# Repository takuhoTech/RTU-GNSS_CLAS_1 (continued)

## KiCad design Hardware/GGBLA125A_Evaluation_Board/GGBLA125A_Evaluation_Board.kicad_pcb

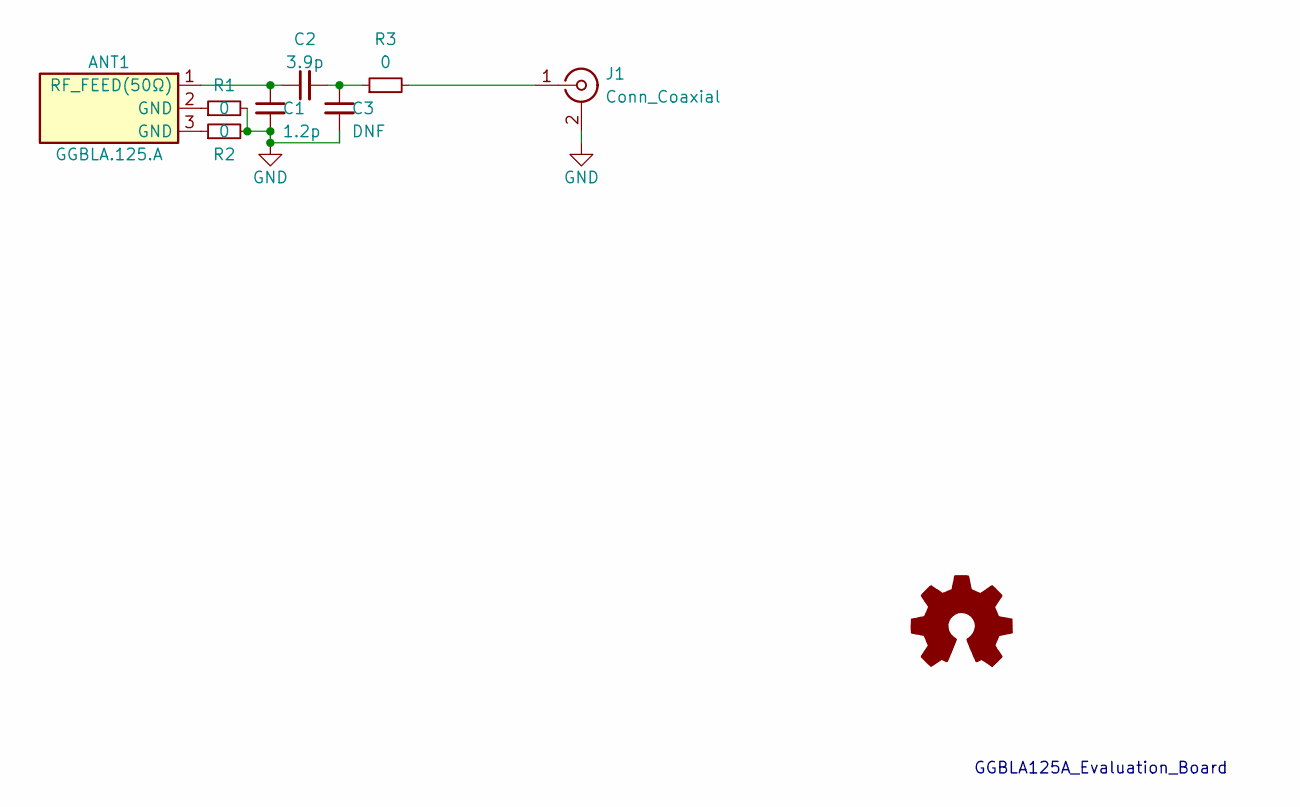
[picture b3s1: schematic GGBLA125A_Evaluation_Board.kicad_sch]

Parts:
ANT1: GGBLA.125.A; Manufacturer_Part_Number GGBLA.125.A; Mouser Part Number 960-GGBLA.125.A
C1: 1.2p; C_0402_1005Metric
C2: 3.9p; C_0402_1005Metric
C3: DNF; C_0402_1005Metric
J1: Conn_Coaxial; SMA_Samtec_SMA-J-P-X-ST-EM1_EdgeMount
R1, R2, R3: 0; R_0402_1005Metric

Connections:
GND: C1.2, C3.2, J1.2 (Ext), R1.2, R2.2
unnamed: ANT1.1 (RF_FEED(50Ω)), C1.1, C2.1
unnamed: ANT1.2 (GND), R1.1
unnamed: ANT1.3 (GND), R2.1
unnamed: C2.2, C3.1, R3.1
unnamed: J1.1 (In), R3.2

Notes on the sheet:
GGBLA125A_Evaluation_Board

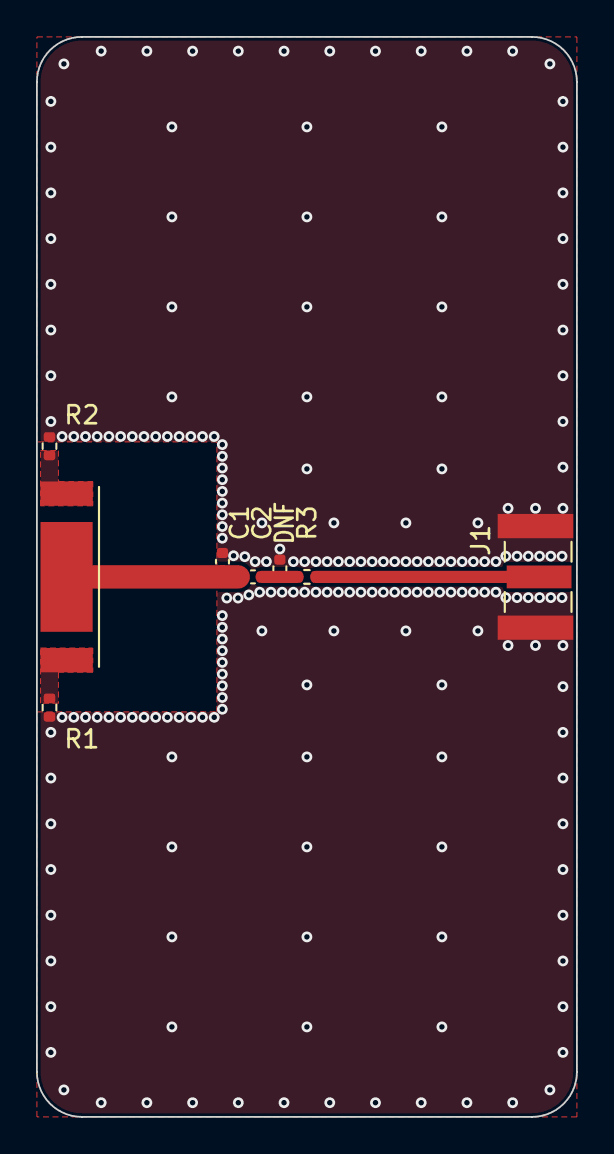
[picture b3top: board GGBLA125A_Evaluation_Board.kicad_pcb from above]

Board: 4 copper layers, 30.0 x 60.0 mm, 8 parts (0 on the bottom side), 6 nets.

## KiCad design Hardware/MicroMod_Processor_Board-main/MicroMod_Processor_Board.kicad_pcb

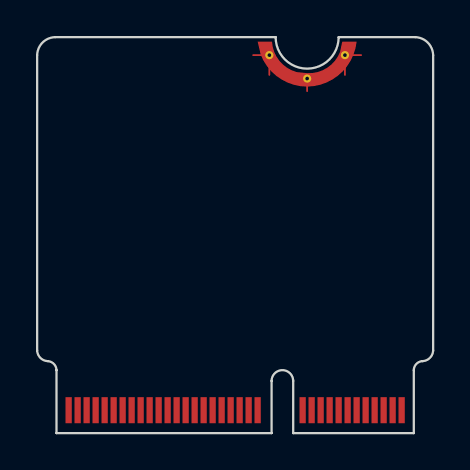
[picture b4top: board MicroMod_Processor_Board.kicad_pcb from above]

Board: 4 copper layers, 22.0 x 22.0 mm, 4 parts (0 on the bottom side), 6 nets, no tracks yet.

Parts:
FRAME1: FRAME-LEDGER; CREATIVE_COMMONS
J1: MICROMOD-2222; M.2-CARD-E-22
LOGO1: SPECIAL_INSTRUCTIONS-ORDERING; ORDERING_INSTRUCTIONS
LOGO3: OSHW-LOGOS; OSHW-LOGO-S

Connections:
3.3V: J1.2, J1.74
/16-G4/RX1/AUD_IN: J1.19, J1.48, J1.54
/17-G3/TX1/AUD_OUT: J1.17, J1.46, J1.56
/25-G1/AUD_LRCLK/SCL1: J1.42, J1.52, J1.53
/26-G2/AUD_BCLK/SDA1: J1.44, J1.50, J1.51
GND: J1.1, J1.7, J1.33, J1.36, J1.39, J1.45, J1.75, J1.GND1, J1.GND2, J1.GND3

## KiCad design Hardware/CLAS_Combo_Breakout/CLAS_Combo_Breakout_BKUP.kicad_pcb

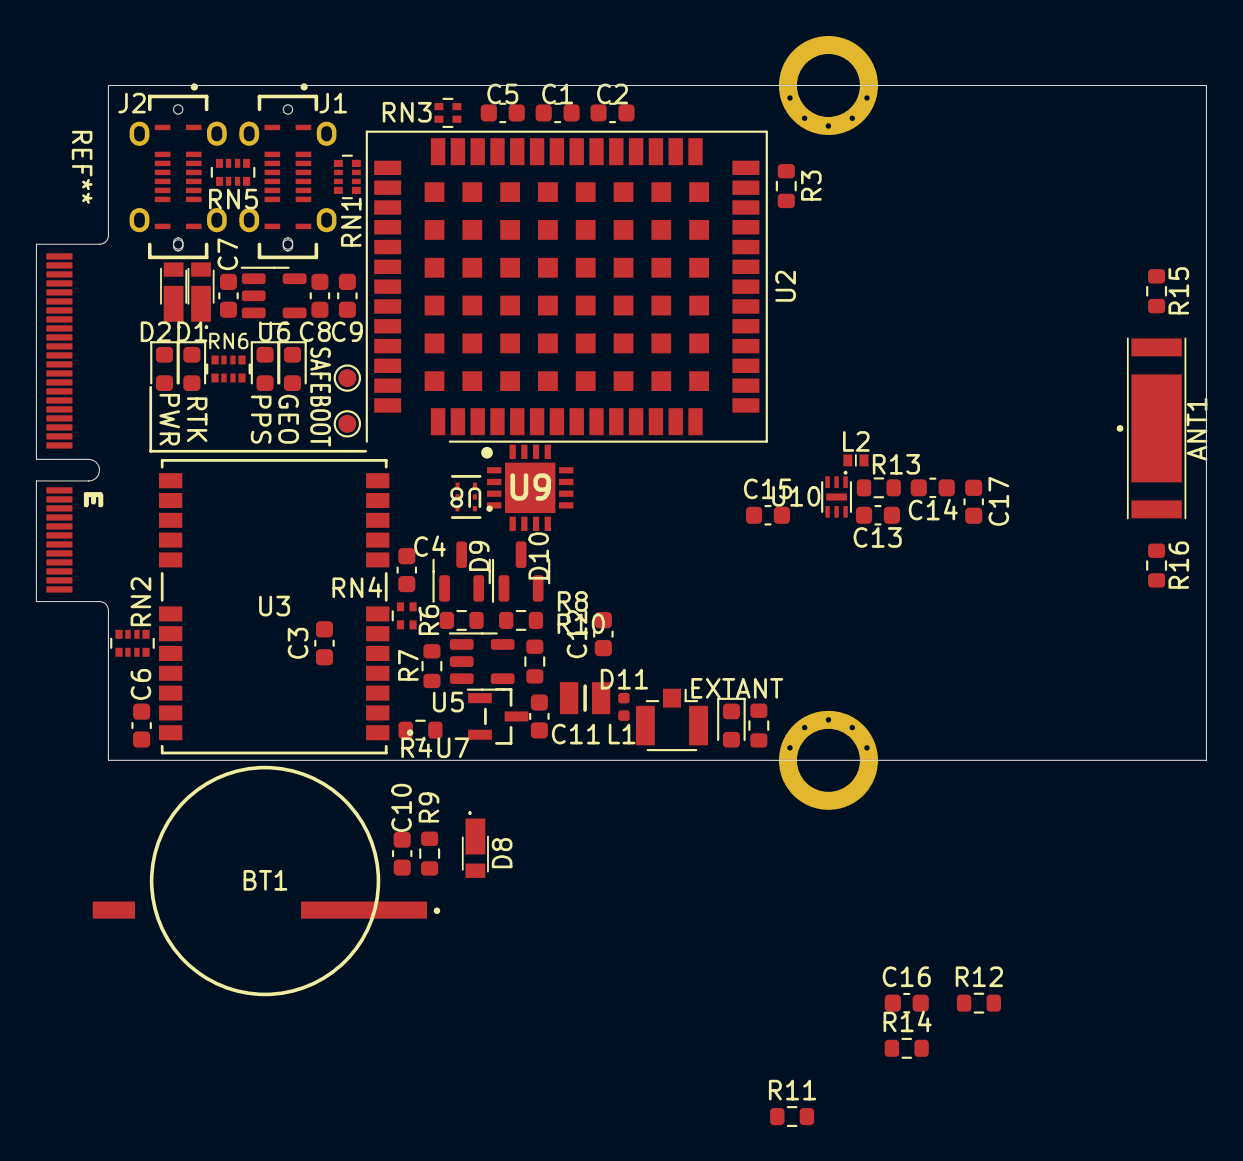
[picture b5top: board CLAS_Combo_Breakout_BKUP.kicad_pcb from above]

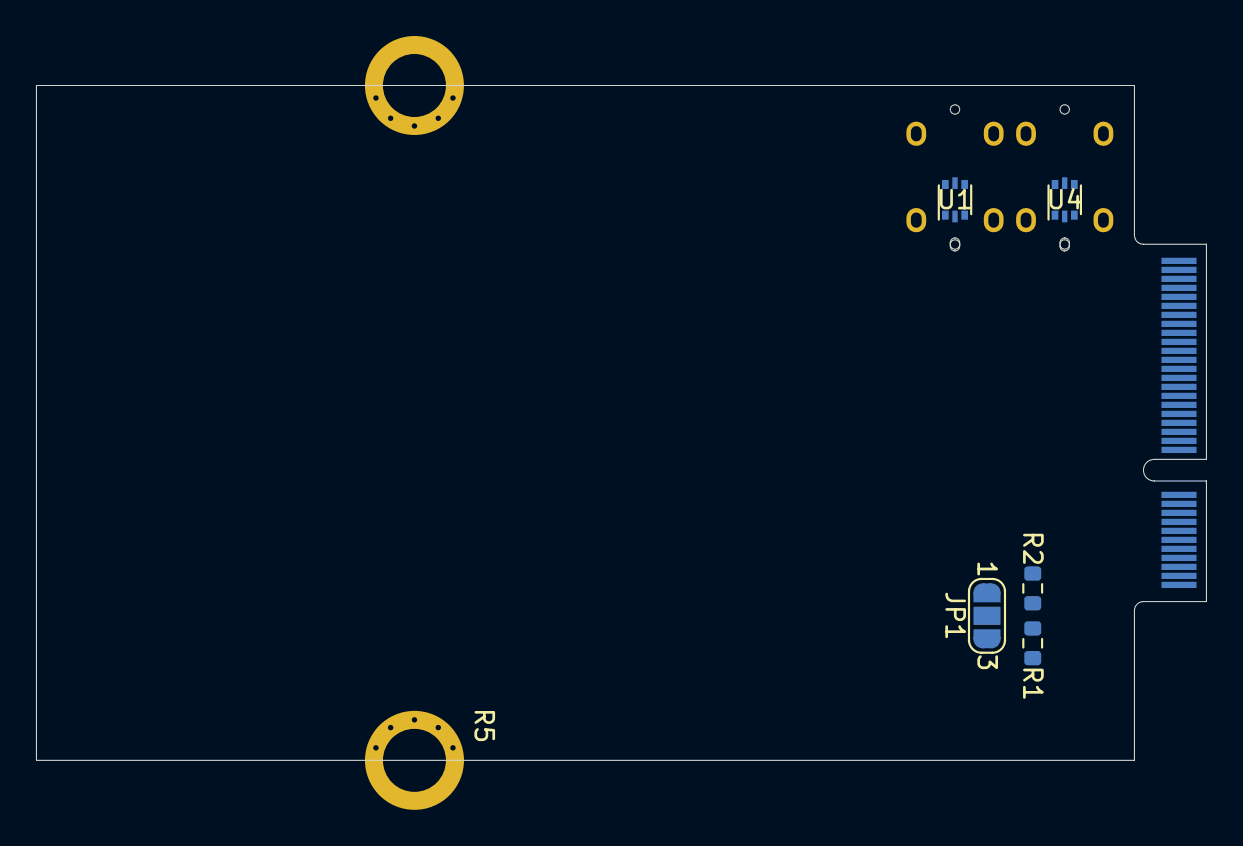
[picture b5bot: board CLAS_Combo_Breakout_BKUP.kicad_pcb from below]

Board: 4 copper layers, 65.0 x 37.5 mm, 70 parts (5 on the bottom side), 66 nets, no tracks yet.

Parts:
ANT1: GGBLA.125.A
BT1: ML-1220_F1AN
C1, C3, C5, C6, C7, C8, C10: 1u; C_0603_1608Metric
C2, C4, C9, C11, C16: 0.1u; C_0603_1608Metric
C12, C15: 47p; C_0603_1608Metric
C13: 1000p; C_0603_1608Metric
C14: 3.9p; C_0603_1608Metric
C17: 1.2p; C_0603_1608Metric
D1, D2, D8: CUHS20S30
D3: RTK; LED_0603_1608Metric
D4: EXTANT; LED_0603_1608Metric
D5: POWER; LED_0603_1608Metric
D6: GEO; LED_0603_1608Metric
D7: PPS; LED_0603_1608Metric
D9: BAS19; SOT-23
D10: BAT54W; SOT-23
D11: PESD0402-140; D_0402_1005Metric
J1, J2: USB_C_Receptacle_USB2.0; USB_C_Receptacle_GCT_USB4120-03-C
J3: Conn_SMA; U.FL_Hirose_U.FL-R-SMT-1_Vertical
JP1: I2C; SolderJumper-3_P1.3mm_Open_RoundedPad1.0x1.5mm_NumberLabels
L1: LQW2BANR12J00L
L2: LQW15AN9N5G00D
R1, R2: 2.2k; R_0603_1608Metric
R3, R4: 33; R_0603_1608Metric
R5: 1k; R_0603_1608Metric
R6: 68; R_0603_1608Metric
R7: 3; R_0603_1608Metric
R8: 22k; R_0603_1608Metric
R9: 1.4k; R_0603_1608Metric
R10: 1.5k; R_0603_1608Metric
R11, R12: 100; R_0603_1608Metric
R13, R15, R16: 0; R_0603_1608Metric
R14: 10k; R_0603_1608Metric
RN1, RN2: 33; R_Array_Convex_4x0402
RN3, RN4: 27; R_Array_Convex_2x0402
RN5: 5.1k; R_Array_Convex_4x0402
RN6: 1k; R_Array_Convex_4x0402
TP1: SAFEBOOT_ZED; TestPoint_Pad_D1.0mm
TP2: SAFEBOOT_NEO; TestPoint_Pad_D1.0mm
U1, U4: USBLC6-2P6; SOT-666
U2: ZED-F9P; ublox_ZED
U3: NEO-D9C-00B; NEO-D9
U5: LMV331; SOT-23-5
U6: AP2112K-3.3; SOT-23-5
U7: DSS20200; DSS20200L-7
U8: PD0922J5050S2HF; PD0922J5050S2HF_ANA
U9: QFN65P400X400X100-17N-D; F2933NBGP
U10: NT1191GEAE3S

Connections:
+3.3V: C1.1, C2.1, C3.1, C4.1, C5.2, C6.2, C8.1, C9.1, C13.1, C16.1, D8.2 (A), JP1.2 (C), RN6.7 (R2.2), RN6.8 (R1.2), U2.33 (VCC), U2.34 (VCC), U2.38 (V_USB), U3.7 (V_USB), U3.23 (VCC), U5.5 (V+), U6.5 (VOUT), U9.1 (VDD), U10.1 (VCTL), U10.5 (VDD)
+3.3V_RF: D9.1 (A), R6.1, R7.2, U3.9 (VCC_RF)
+5V: C7.1, D1.1 (K), D2.1 (K), U6.1 (VIN), U6.3 (EN)
/ANT_NEO: R11.2, U3.11 (RF_IN), U8.6 (OUT2)
/ANT_ZED: R11.1, U2.2 (RF_IN), U8.4 (OUT1)
/CC1_NEO: J2.A5 (CC1), RN5.6 (R3.2)
/CC1_ZED: J1.A5 (CC1), RN5.8 (R1.2)
/CC2_NEO: J2.B5 (CC2), RN5.5 (R4.2)
/CC2_ZED: J1.B5 (CC2), RN5.7 (R2.2)
/D+NEO: J2.A6 (D+), J2.B6 (D+), RN4.2 (R2.1), U4.4 (I/O2)
/D+ZED: J1.A6 (D+), J1.B6 (D+), RN3.4 (R1.2), U1.4 (I/O2)
/D-NEO: J2.A7 (D-), J2.B7 (D-), RN4.1 (R1.1), U4.6 (I/O1)
/D-ZED: J1.A7 (D-), J1.B7 (D-), RN3.3 (R2.2), U1.6 (I/O1)
/EXTANT_DETECT: R5.1, R12.2, R14.2, U5.4
/GEO: RN6.6 (R3.2), U2.19 (GEOFENCE_STAT)
/RESET: U2.49 (~RESET), U3.8 (~RESET)
/RTK: D3.1 (K), U2.20 (RTK_STAT)
/SCL: R1.2, RN1.3 (R3.1), RN2.5 (R4.2)
/SCL_NEO_: RN2.4 (R4.1), U3.19 (SCL/SPI_SLK)
/SCL_ZED_: RN1.6 (R3.2), U2.45 (SCL/SPI_CLK)
/SDA: R2.2, RN1.2 (R2.1), RN2.6 (R3.2)
/SDA_NEO_: RN2.3 (R3.1), U3.18 (SDA/~SPI_CS)
/SDA_ZED_: RN1.7 (R2.2), U2.44 (SDA/~SPI_CS)
/TP: RN6.5 (R4.2), U2.53 (TIMEPULSE)
/TXD1_NEO_: RN2.2 (R2.1), U3.20 (TXD1/SPI_MISO)
/TXD1_ZED_: RN1.8 (R1.2), U2.42 (TXD/SPI_MISO)
/TX_RDY_: RN1.5 (R4.2), U2.46 (TX_READY)
/VBUS_NEO: D2.2 (A), J2.A4 (VBUS), J2.A9 (VBUS), J2.B4 (VBUS), J2.B9 (VBUS), U4.5 (VBUS)
/VBUS_ZED: D1.2 (A), J1.A4 (VBUS), J1.A9 (VBUS), J1.B4 (VBUS), J1.B9 (VBUS), U1.5 (VBUS)
/V_BACKUP: BT1.1 (+), C10.1, R9.2, U2.36 (V_BCKP)
GND: BT1.2 (-), C1.2, C2.2, C3.2, C4.2, C5.1, C6.1, C7.2, C8.2, C9.2, C10.2, C11.1, C13.2, C16.2, C17.2, D4.1 (K), D5.1 (K), D6.1 (K), D7.1 (K), D11.1 (A1), J1.A1 (GND), J1.A12 (GND), J1.B1 (GND), J1.B12 (GND), J1.S1 (SHIELD), J2.A1 (GND), J2.A12 (GND), J2.B1 (GND), J2.B12 (GND), J2.S1 (SHIELD), J3.2 (Ext), R8.2, R10.1, R14.1, R15.2, R16.2, RN2.1 (R1.1), RN2.8 (R1.2), RN5.1 (R1.1), RN5.2 (R2.1), RN5.3 (R3.1), RN5.4 (R4.1), U1.2 (GND), U2.1 (GND), U2.3 (GND), U2.12 (GND), U2.14 (GND), U2.32 (GND), U2.37 (GND), U2.41 (GND), U2.48 (GND), U2.55 (GND), U3.10 (GND), U3.12 (GND), U3.13 (GND), U3.24 (GND), U4.2 (GND), U5.2 (V-), U6.2 (GND), U8.1 (GND), U8.3 (GND), U8.5 (GND), U9.4 (GND), U9.5 (GND), U9.6 (GND), U9.7 (GND), U9.8 (GND), U9.10 (GND), U9.11 (GND), U9.13 (GND), U9.14 (GND), U9.15 (GND), U9.17 (EP), U10.3 (GND), U10.6 (NC(GND)), U10.7 (EP)
unnamed: ANT1.1 (RF_FEED(50Ω)), C14.1, C17.1
unnamed: ANT1.2 (GND), R15.1
unnamed: ANT1.3 (GND), R16.1
unnamed: C11.2, L1.1, U7.3 (C)
unnamed: C12.2, U9.9 (RF2)
unnamed: C14.2, R13.1
unnamed: C15.1, U9.12 (RF1)
unnamed: D3.2 (A), RN6.1 (R1.1)
unnamed: D4.2 (A), R5.2
unnamed: D5.2 (A), RN6.2 (R2.1)
unnamed: D6.2 (A), RN6.3 (R3.1)
unnamed: D7.2 (A), RN6.4 (R4.1)
unnamed: D8.1 (K), R9.1
unnamed: D9.3 (K), D10.1 (A)
unnamed: D10.3 (K), R10.2, U7.1 (B)
unnamed: C12.1, D11.2 (A2), J3.1 (In), L1.2
unnamed: JP1.1 (A), R2.1
unnamed: JP1.3 (B), R1.1
unnamed: L2.1, R13.2
unnamed: L2.2, U10.2 (RFIN)
unnamed: R3.1, U2.27 (TXD2)
unnamed: R3.2, U3.4 (RXD2)
unnamed: R4.1, U2.26 (RXD2)
unnamed: R4.2, U3.3 (TXD2)
unnamed: R6.2, R8.1, U5.1 (+)
unnamed: R7.1, U5.3 (-), U7.2 (E)
unnamed: R12.1, U9.2 (VCTL)
unnamed: RN3.1 (R1.1), U2.40 (USB_D+)
unnamed: RN3.2 (R2.1), U2.39 (USB_D-)
unnamed: RN4.3 (R2.2), U3.6 (USB_D+)
unnamed: RN4.4 (R1.2), U3.5 (USB_D-)
unnamed: TP1.1, U2.50 (~SAFEBOOT)
unnamed: TP2.1, U3.1 (~SAFEBOOT)
unnamed: U8.2 (IN), U9.3 (RFC)
unnamed: C15.2, U10.4 (RFOUT)

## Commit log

2023-08-14 Add module and start wiring
2023-08-17 add LNA
2023-08-18 受信回路完成
2023-08-18 update schematic
2023-08-19 フットプリントの仮割り当てが完了
2023-08-20 フットプリントの文字サイズを調整、3Dモデルを割当
2023-08-20 部品を配置
2023-08-21 3Dモデルを変更
2023-08-23 アンテナ電源供給回路を配置
2023-09-11 RFリレーとスプリッタを置き換え
2023-09-14 シルクを調整
2023-09-18 change BAT and USB_C
2023-09-19 配置仮完了
2023-09-20 配置完了
2023-09-25 LEDの配置を調整
2023-09-26 LED周りを配線
2023-09-26 LED周りの配線を調整
2023-09-27 部品配置を調整
2023-09-28 ZED側のUSB周りを配線
2023-10-01 I2C系統を配線
2023-10-03 配線中、残り3V3
2023-10-03 3V3パスを配線、ZED周辺のパスを改善したい
2023-10-04 配線パスを改善
2023-10-05 配線を迂回中
2023-10-07 GNDベタをクリアランス0.2mmで配置
2023-10-08 伝送線路を配線中
2023-10-08 伝送線路を配線
2023-10-09 伝送線路にビアを配置part1
2023-10-13 アンテナ設計中
2023-10-13 アンテナ周りを配線
2023-10-13 伝送線路配線完了
2023-10-14 上半分にビアを配置
2023-10-16 配線パスを修正
2023-10-16 外周ビア置き完了
2023-10-17 ビア配置完了、残微調整
2023-10-20 プルダウンRをプルアップRに変更、EANTのLEDを移動
2023-10-24 アンテナのFootprintをデータシートに準拠
2023-10-25 トランジスタの記号をQに変更、REFを整理
2023-10-26 アンテナ伝送路0.678mmバージョン
2023-10-27 アンテナのマッチング回路を再設計
2023-10-29 MMCXのフットプリントを作成 ピン表示のシルクの位置調整
2023-10-29 インダクタを変更 フットプリントを追加
2023-10-31 外部アンテナの伝送路を整備
2023-11-02 LNAとスイッチ間の伝送線路を改善
2023-11-02 ビア配置を調整、数日寝かせる
2023-11-03 PD0922のFPを修正 一部再設計中
2023-11-04 伝送線路修整完了。発注秒読み
2023-11-06 電源回路縮小完了
2023-11-10 伝送線路調整中、コンパレータを変更
2023-11-12 発注完了
2023-11-26 add README.pdf
2023-11-26 edit logo
2024-01-25 基板厚を修正、movingbaseアドオンボードの設計を開始
2024-01-27 同軸コネクタのフットプリントを追加
2024-01-28 面実装MMCX雄コネクタのフットプリントを作成
2024-01-30 E220-900T22S(JP)のフットプリントを追加修整
2024-01-31 ISP4520のフットプリントを追加編集
2024-02-01 ISP4520のシンボルを追加、編集
2024-02-01 ISP4520周辺回路を設計中
2024-02-16 電源回路描いた
2024-02-20 カイロズカッコカリ
2024-02-21 アノテーション完了、一部のピンは仮結線
2024-02-22 フットプリントの割り当て完了
2024-03-13 配線４割
2024-03-17 ISP4520の公式のフットプリントの間違いを修正
    メーカーが提供しているフットプリントでも信用しないようにしましょう
2024-03-17 PCBファイルのISP4520フットプリントを正しいものに置換
2024-03-24 ちょっと配線した
2024-04-01 MUXをSP3Tのものに変更しRS485経由での補正データの送受信に対応する回路図を書いた
2024-08-16 一部ライブラリを整理

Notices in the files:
parts and their libraries:
https://creativecommons.org/licenses/by-sa/4.0
Released under the Creative Commons Attribution Share-Alike 4.0 License
